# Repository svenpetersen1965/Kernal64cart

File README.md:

# Kernal64cart
A simple Kernal Cartridge for the Commodore C64, which has to get the /HIRAM signal for functioning 100%

# Status
This is a preliminary release. The cartridge Rev. 2 is fully tested and functional. The documentation is almost complete. The test is not jet documented, which is the reason for calling this a preliminary release.

Find the revision history in the Module Description.

Kernal64cart Rev. 2 in a stumpy Cartridge Case (tfw8bit.com)

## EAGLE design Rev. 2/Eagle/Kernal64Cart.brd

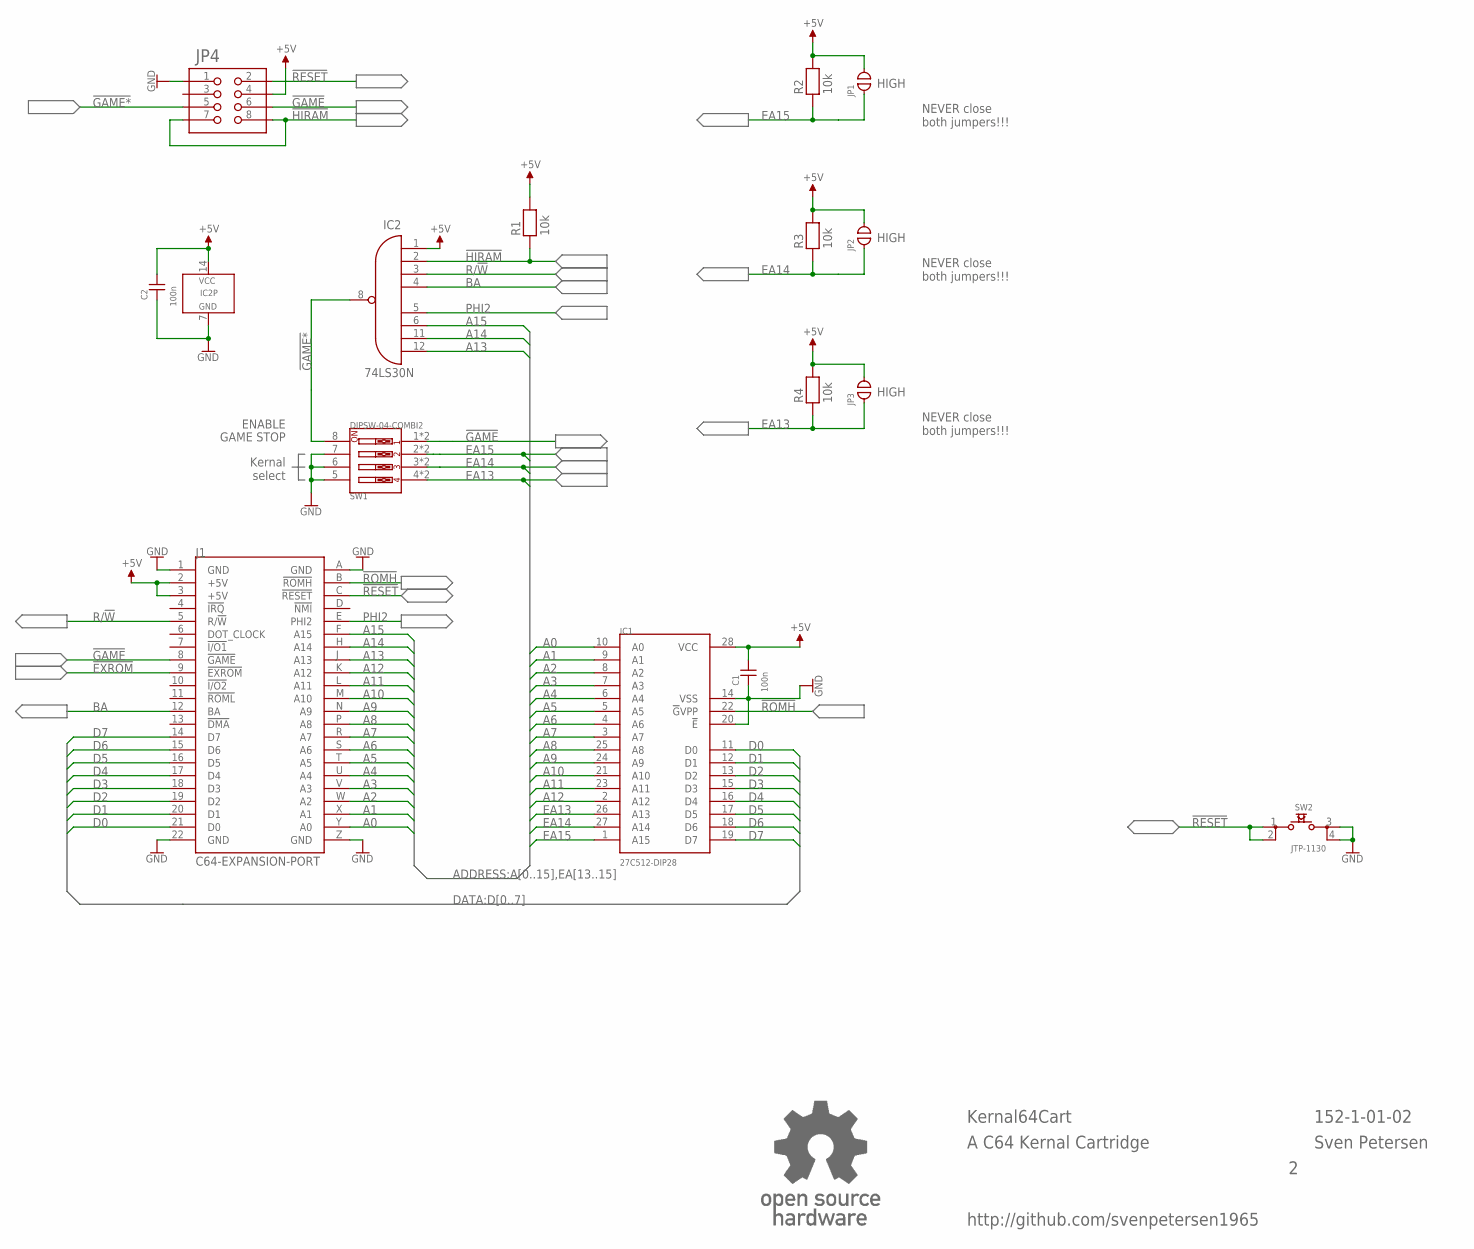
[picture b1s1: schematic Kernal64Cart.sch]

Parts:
C1, C2: 100n; C-2,5
IC1: 27C512-DIP28; DIL28-6
IC2: 74LS30N; DIL-14
J1: C64-EXPANSION-PORT; EXPANSIO_SQ
JP1, JP2, JP3: OPEN; CP_OP
JP4: PINHD-2X490°/MPE_088; 2X04_90_SERIES_088
R1, R2, R3, R4: 10k; R-10
SW1: DIPSW-04-COMBI2; DIPSW-04V-COMBI2
SW2: JTP-1130
U$50: OPEN_SOURCE_HW; OPENHW

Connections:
!EXROM: J1.9 (!EXROM)
!GAME: J1.8 (!GAME), JP4.6, SW1.1, SW1.1A (1)
!GAME*: IC2.8 (O), JP4.5, SW1.8
!HIRAM: IC2.2 (I1), JP4.7, JP4.8, R1.1
!RESET: J1.C (!RESET), JP4.2, SW2.1, SW2.2
!ROMH: IC1.22 (!G!VPP), J1.B (!ROMH)
+5V: C1.2, C2.2, IC1.28 (VCC), IC2.1 (I0), IC2.14 (VCC), J1.2 (+5V), J1.3 (+5V), JP1.2, JP2.2, JP3.2, JP4.4, R1.2, R2.2, R3.2, R4.2
A0: IC1.10 (A0), J1.Y (A0)
A1: IC1.9 (A1), J1.X (A1)
A2: IC1.8 (A2), J1.W (A2)
A3: IC1.7 (A3), J1.V (A3)
A4: IC1.6 (A4), J1.U (A4)
A5: IC1.5 (A5), J1.T (A5)
A6: IC1.4 (A6), J1.S (A6)
A7: IC1.3 (A7), J1.R (A7)
A8: IC1.25 (A8), J1.P (A8)
A9: IC1.24 (A9), J1.N (A9)
A10: IC1.21 (A10), J1.M (A10)
A11: IC1.23 (A11), J1.L (A11)
A12: IC1.2 (A12), J1.K (A12)
A13: IC2.12 (I7), J1.J (A13)
A14: IC2.11 (I6), J1.H (A14)
A15: IC2.6 (I5), J1.F (A15)
BA: IC2.4 (I3), J1.12 (BA)
D0: IC1.11 (D0), J1.21 (D0)
D1: IC1.12 (D1), J1.20 (D1)
D2: IC1.13 (D2), J1.19 (D2)
D3: IC1.15 (D3), J1.18 (D3)
D4: IC1.16 (D4), J1.17 (D4)
D5: IC1.17 (D5), J1.16 (D5)
D6: IC1.18 (D6), J1.15 (D6)
D7: IC1.19 (D7), J1.14 (D7)
EA13: IC1.26 (A13), JP3.1, R4.1, SW1.4, SW1.4A (4)
EA14: IC1.27 (A14), JP2.1, R3.1, SW1.3, SW1.3A (3)
EA15: IC1.1 (A15), JP1.1, R2.1, SW1.2, SW1.2A (2)
GND: C1.1, C2.1, IC1.14 (VSS), IC1.20 (!E), IC2.7 (GND), J1.1 (GND), J1.22 (GND), J1.A (GND), J1.Z (GND), JP4.1, SW1.5, SW1.6, SW1.7, SW2.3, SW2.4
PHI2: IC2.5 (I4), J1.E (PHI2)
R/!W: IC2.3 (I2), J1.5 (R/!W)

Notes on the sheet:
HIGH
NEVER close both jumpers!!!
Kernal64Cart
Sven Petersen
152-1-01-02
ENABLE
GAME STOP
Kernal select
http://github.com/svenpetersen1965
A C64 Kernal Cartridge

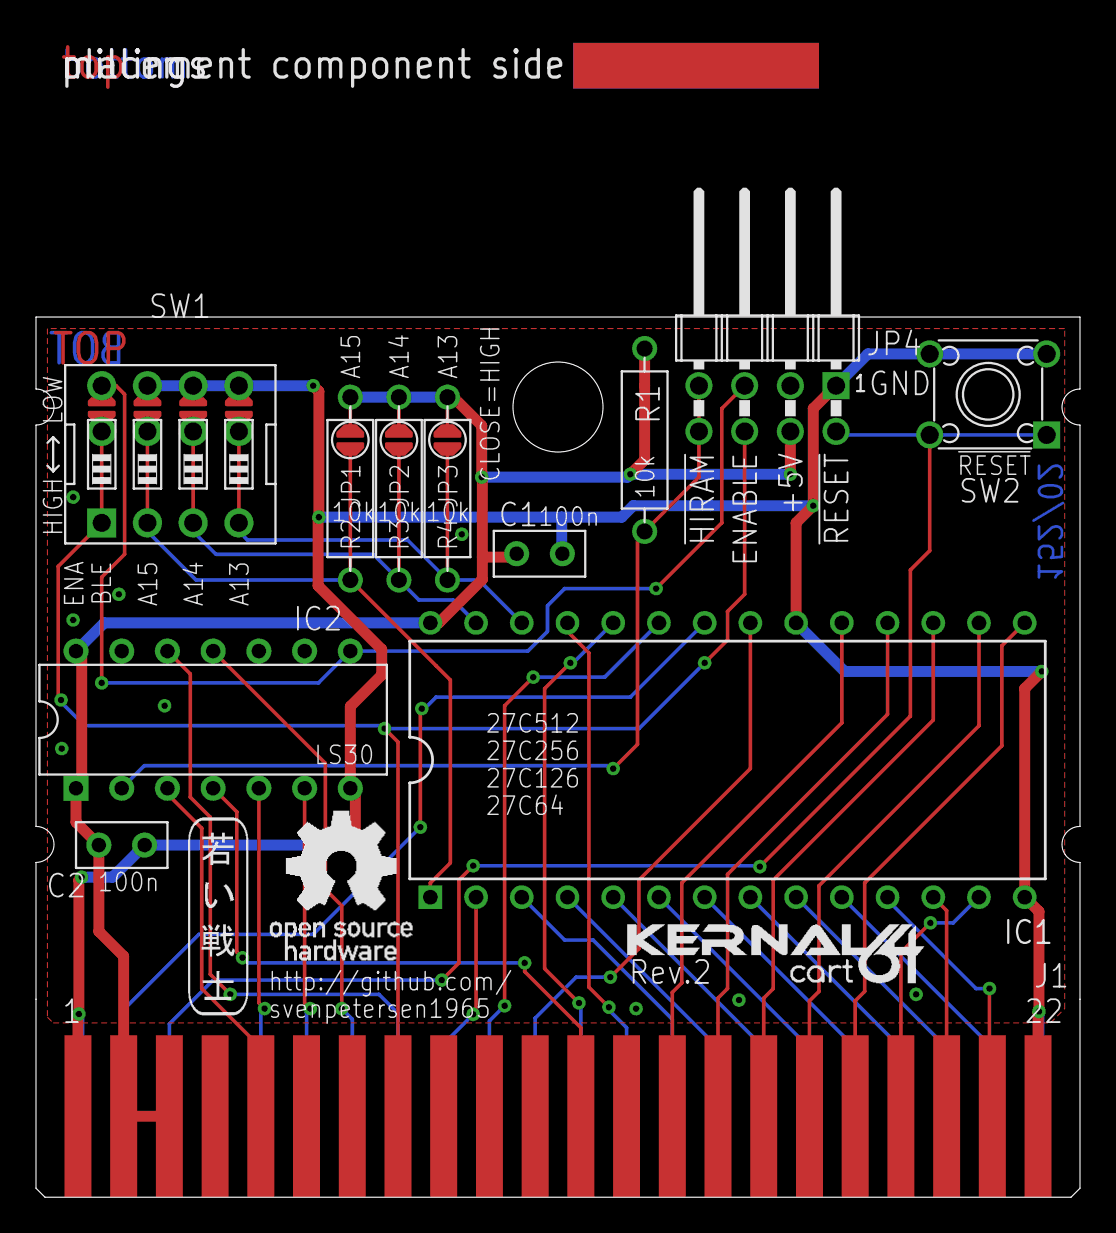
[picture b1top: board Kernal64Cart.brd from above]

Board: 2 copper layers, 58.0 x 64.5 mm, 20 parts (0 on the bottom side), 37 nets.

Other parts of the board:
U$39: KERNAL64CART
U$40: 2LAYER
U$41: PCB-TITLE/
U$42: SVEN_TAG

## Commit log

2023-01-21 Peliminary release
2023-01-21 not used
2023-01-21 Preliminary Documentation Rev. 2
